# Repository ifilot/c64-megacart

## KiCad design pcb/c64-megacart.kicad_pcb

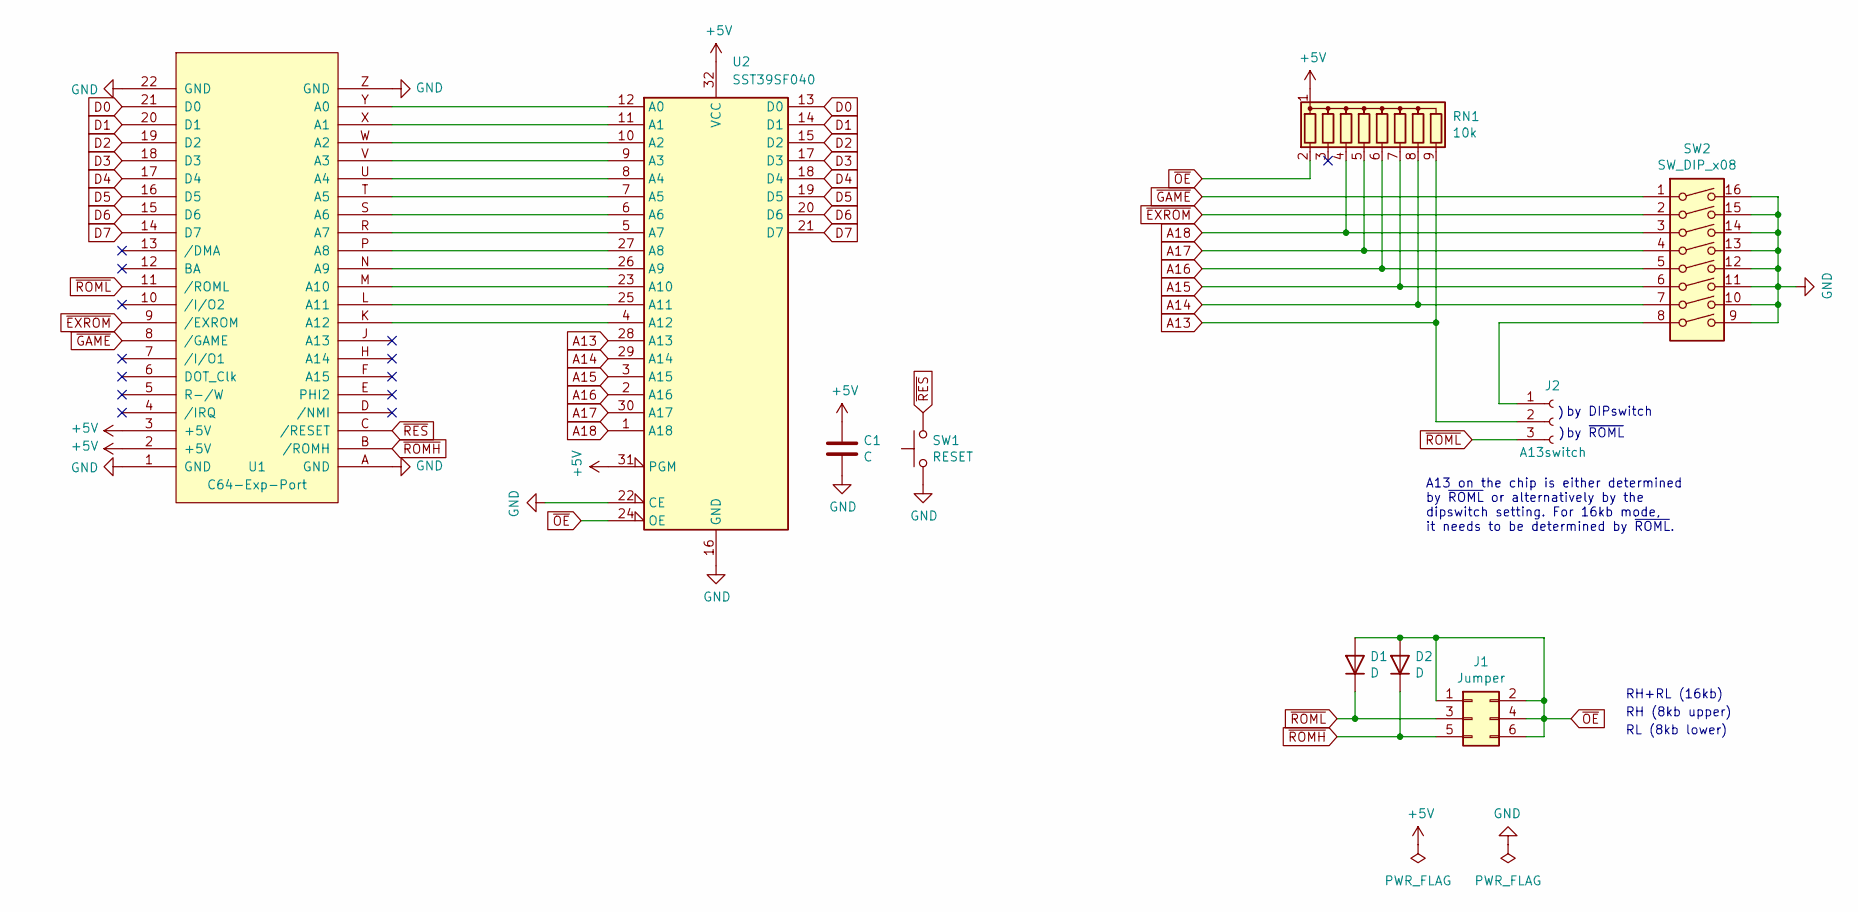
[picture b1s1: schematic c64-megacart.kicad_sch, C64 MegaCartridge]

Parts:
C1: C; C_Disc_D5.0mm_W2.5mm_P5.00mm
D1, D2: D; D_DO-35_SOD27_P7.62mm_Horizontal
J1: Jumper; PinHeader_2x03_P2.54mm_Vertical
J2: A13switch; PinHeader_1x03_P2.54mm_Vertical
RN1: 10k; R_Array_SIP9
SW1: RESET; SW_PUSH_6mm
SW2: SW_DIP_x08; SW_DIP_SPSTx08_Slide_9.78x22.5mm_W7.62mm_P2.54mm
U1: C64-Exp-Port; C64-Cart
U2: SST39SF040

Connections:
+5V: C1.1, RN1.1 (common), U1.2 (+5V), U1.3 (+5V), U2.31 (PGM), U2.32 (VCC)
A13: J2.2, RN1.9 (R8), U2.28 (A13)
A14: RN1.8 (R7), SW2.7, U2.29 (A14)
A15: RN1.7 (R6), SW2.6, U2.3 (A15)
A16: RN1.6 (R5), SW2.5, U2.2 (A16)
A17: RN1.5 (R4), SW2.4, U2.30 (A17)
A18: RN1.4 (R3), SW2.3, U2.1 (A18)
D0: U1.21 (D0), U2.13 (D0)
D1: U1.20 (D1), U2.14 (D1)
D2: U1.19 (D2), U2.15 (D2)
D3: U1.18 (D3), U2.17 (D3)
D4: U1.17 (D4), U2.18 (D4)
D5: U1.16 (D5), U2.19 (D5)
D6: U1.15 (D6), U2.20 (D6)
D7: U1.14 (D7), U2.21 (D7)
GND: C1.2, SW1.1, SW2.9, SW2.10, SW2.11, SW2.12, SW2.13, SW2.14, SW2.15, SW2.16, U1.1 (GND), U1.22 (GND), U1.A (GND), U1.Z (GND), U2.16 (GND), U2.22 (CE)
unnamed: J2.1, SW2.8
unnamed: U1.K (A12), U2.4 (A12)
unnamed: U1.L (A11), U2.25 (A11)
unnamed: U1.M (A10), U2.23 (A10)
unnamed: U1.N (A9), U2.26 (A9)
unnamed: U1.P (A8), U2.27 (A8)
unnamed: U1.R (A7), U2.5 (A7)
unnamed: U1.S (A6), U2.6 (A6)
unnamed: U1.T (A5), U2.7 (A5)
unnamed: U1.U (A4), U2.8 (A4)
unnamed: U1.V (A3), U2.9 (A3)
unnamed: U1.W (A2), U2.10 (A2)
unnamed: U1.X (A1), U2.11 (A1)
unnamed: U1.Y (A0), U2.12 (A0)
~EXROM: SW2.2, U1.9 (/EXROM)
~GAME: SW2.1, U1.8 (/GAME)
~OE: D1.2 (A), D2.2 (A), J1.1, J1.2, J1.4, J1.6, RN1.2 (R1), U2.24 (OE)
~RES: SW1.2, U1.C (/RESET)
~ROMH: D2.1 (K), J1.5, U1.B (/ROMH)
~ROML: D1.1 (K), J1.3, J2.3, U1.11 (/ROML)

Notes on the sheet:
by ~{ROML}
RH (8kb upper)
RL (8kb lower)
A13 on the chip is either determined by ~{ROML} or alternatively by the dipswitch setting. For 16kb mode, it needs to be determined by ~{ROML}.
by DIPswitch
RH+RL (16kb)

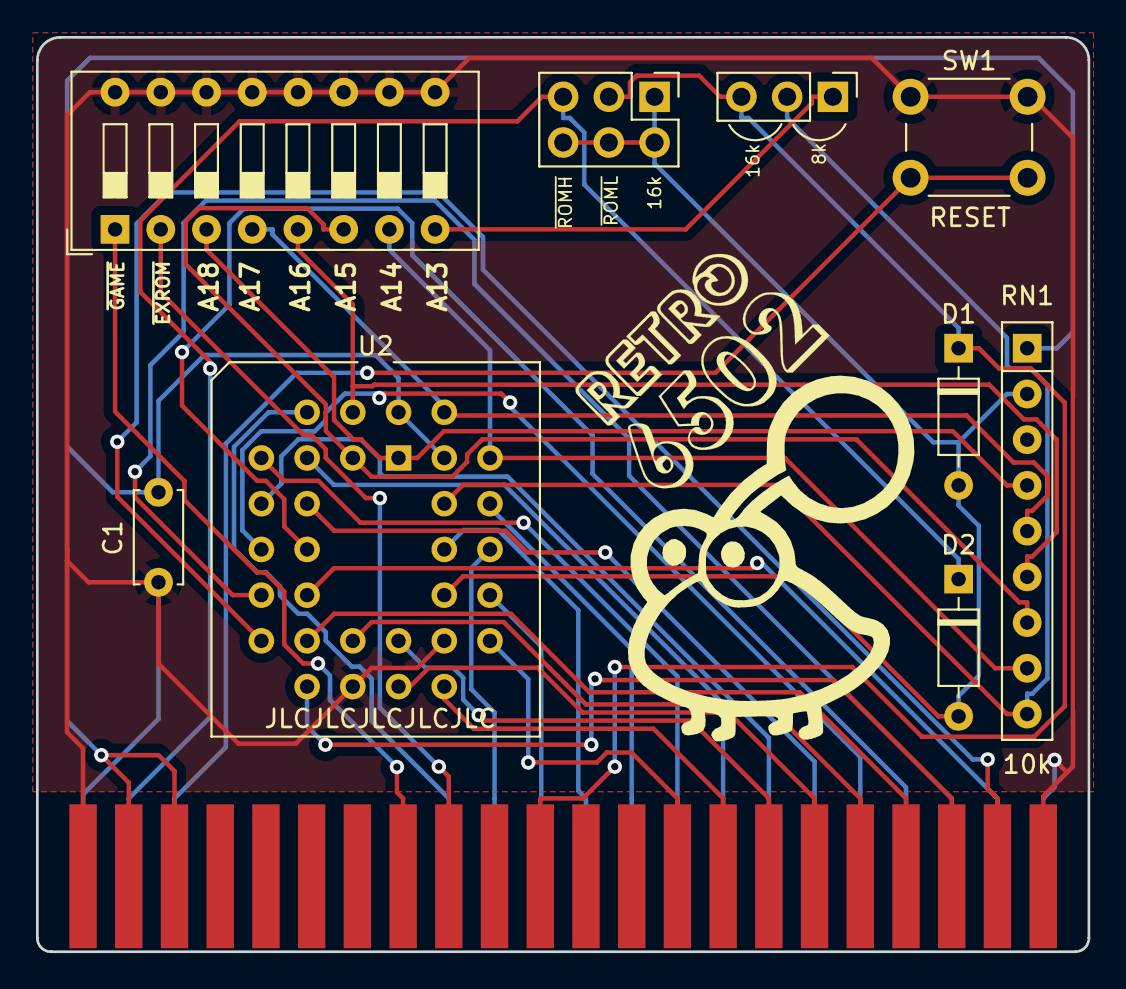
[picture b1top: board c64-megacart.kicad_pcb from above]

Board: 2 copper layers, 58.4 x 50.8 mm, 11 parts (0 on the bottom side), 36 nets.

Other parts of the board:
G001: LOGO; puni

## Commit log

2024-09-02 Changing design
